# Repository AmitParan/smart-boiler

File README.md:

# Smart Electric Boiler — דוד חשמלי חכם

**An autonomous retrofit energy-management system for domestic electric water heaters.**

Final engineering project · Afeka College of Engineering, Tel Aviv
Students: **Elad Moalem** (אלעד מועלם) · **Amit Paran** (עמית פארן)
Supervisor: **Dmitry Teif** (דמיטרי טייף)

**Communication:** Master ↔ slave over **Power Line Communication** (KQ-330
modems on the 220 VAC wiring) — the default build. A WiFi (UDP) transport is
available as an option.

> ### 👨‍🏫 Reviewing this project? Start with the **[Guided Code Tour →](CODE_TOUR.md)**
> A short walkthrough of the safety architecture, the FreeRTOS mutex design, the
> wire protocol and the transport abstraction — each claim shown alongside the
> few lines of code that prove it, plus **four checks you can reproduce yourself**
> on the hardware in under ten minutes.

---

## Table of contents

1. [The problem](#1-the-problem)
2. [The solution — two-tier hybrid heating](#2-the-solution--two-tier-hybrid-heating)
3. [System architecture](#3-system-architecture)
4. [Hardware](#4-hardware)
5. [Safety architecture](#5-safety-architecture)
6. [Communication](#6-communication)
7. [Firmware architecture (FreeRTOS)](#7-firmware-architecture-freertos)
8. [The control brain](#8-the-control-brain)
9. [Repository layout](#9-repository-layout)
10. [Build and flash](#10-build-and-flash)
11. [Demo mode — 8 automated scenarios](#11-demo-mode--8-automated-scenarios)
12. [Results](#12-results)
13. [Documentation index](#13-documentation-index)

---

## 1. The problem

A conventional Israeli electric boiler ("דוד חשמלי") is a **blind, open-loop
machine**. The user flips a switch, waits, and gets no feedback about water
temperature or how much hot water is actually available. Three physical
inefficiencies follow from that:

| Problem | Consequence |
|---|---|
| **Open-loop operation** | The user over-heats "just in case", or under-heats and gets a cold shower |
| **Standing thermal losses** | A 80–150 L tank held at high temperature bleeds heat to the room continuously, 24 h a day |
| **Whole-tank heating** | Washing your hands heats 150 L of water to serve 2 L of demand |

The obvious fix — a **tankless instant heater** — is not available to most Israeli
homes. Those units demand **14 kW–24 kW** and three-phase service. A standard
apartment is limited to **single-phase, 16 A ≈ 3 kW**.

## 2. The solution — two-tier hybrid heating

This project fits **within the 3 kW household ceiling** by splitting the job
across two coordinated heating tiers instead of one big element.

```
   ┌──────────────────────────────────────────────────────────────┐
   │  TIER 1 — Moderate Storage                                   │
   │  Hold the main tank at only 35–40 °C, not 60–70 °C.          │
   │  A cooler tank loses far less heat to the room, so standing   │
   │  losses collapse. The tank is a warm buffer, not a kettle.    │
   └──────────────────────────────────────────────────────────────┘
                                │  water leaves the tank at ~35-40 °C
                                ▼
   ┌──────────────────────────────────────────────────────────────┐
   │  TIER 2 — Flow-Triggered Top-Up                              │
   │  A 3000 W inline heater in series with the outlet pipe adds   │
   │  a focused +3-7 °C ONLY while water is actually flowing,      │
   │  and only under hardware interlock. Energy is spent on the    │
   │  water you are using, at the moment you use it.               │
   └──────────────────────────────────────────────────────────────┘
```

The tank never has to be hot — it only has to be *warm enough* that a 3 kW
inline booster can close the remaining gap in real time. That is what keeps the
system inside a single-phase 16 A supply while still delivering a hot shower.

On top of the thermodynamics sits an **adaptive learning layer** that records
when the household actually showers and pre-heats ahead of predicted demand,
so the tank is ready without being held hot all day.

## 3. System architecture

Two microcontrollers, deliberately separated by role:

```
┌───────────────────────────────┐              ┌───────────────────────────────┐
│  MASTER — indoor command unit │              │  SLAVE — boiler-side unit     │
│  ESP32-S3                     │              │  ESP32-C6                     │
│  Viewe UEDX80480050E-WB-A     │◄────────────►│  custom PCB                   │
│  800x480 capacitive touch     │   1 packet   │                               │
│                               │   per second │                               │
│  · LVGL v8 touchscreen HMI    │              │  · 3x DS18B20 temperature     │
│  · SystemManager state machine│              │  · YF-B6 flow sensor          │
│  · Smart preheat learning     │              │  · ACS758 current sensing     │
│  · WiFi / NTP / weather       │              │  · 2x SSR drive (burst PWM)   │
│  · 8-scenario demo bench      │              │  · analog hardware interlock  │
└───────────────────────────────┘              └───────────────────────────────┘
        the user's world                              the plumbing's world
```

**Why two units?** The boiler is usually in a service balcony or on the roof —
behind reinforced concrete, often inside or near a MAMAD (safe room). Putting
the touchscreen there would be useless, and relying on WiFi reaching there was
judged unsafe for a control link. The control link therefore runs over **the
building's own 220 VAC wiring** using **Power Line Communication (PLC)**, which
passes through concrete that WiFi cannot.

> **Transport options.** PLC over KQ-330 modems is the default link. The
> communication layer is abstracted, so the same firmware can alternatively run
> the link over **WiFi (UDP)** with a single build flag, carrying byte-identical
> packets. Everything above the transport is shared by both options
> (see [section 6](#6-communication)).

## 4. Hardware

### 4.1 Slave GPIO map — ESP32-C6 *(book Table 7)*

| GPIO | Function | Direction | Component |
|:---:|---|---|---|
| **4** | `SSR_Internal` | Output (PWM) | Tank heater SSR |
| **5** | `SSR_Boost` | Output (PWM) | Inline booster SSR |
| **7** | `One_Wire_Bus` | In/Out | 3 × DS18B20 on one bus |
| **6** | `Flow_Sensor` | Input (interrupt) | YF-B6 Hall-effect flow meter |
| **10** | `PLC_RX` | Input (UART) | KQ-330 DOUT, via level shifter U3 |
| **11** | `PLC_TX` | Output (UART) | KQ-330 DIN |
| **3** | `Current_ADC` | Input (analog) | ACS758LCB-050B |

Defined in [`slave/src/config/config.h`](slave/src/config/config.h).

### 4.2 Master GPIO map — ESP32-S3 *(book Table 9)*

| GPIO | Function | Direction | Component |
|:---:|---|---|---|
| **17** | `MASTER_TX_PIN` | Output | KQ-330 DIN |
| **13** | `MASTER_RX_PIN` | Input | KQ-330 DOUT |
| **43 / 44** | `UART0_TX/RX` | — | USB CDC debug console |
| — | Touch + RGB | — | Managed by the board package (800×480) |

Defined in [`master/src/config/config.h`](master/src/config/config.h).

### 4.3 Key components

| Component | Part | Role |
|---|---|---|
| Master MCU | ESP32-S3 (Viewe UEDX80480050E-WB-A) | HMI, decisions, connectivity |
| Slave MCU | ESP32-C6-DevKitC-1 | Sensing, switching, safety |
| Power-line modem | KQ-330 | 9600 bps UART over 220 VAC |
| Solid-state relays | SSR-40DA (zero-crossing) | Switch both heating elements |
| Temperature | 3 × DS18B20 (1-Wire) | Tank, boiler outlet, boost outlet |
| Flow | YF-B6 Hall-effect | `F = 6.6 × Q` (Hz per L/min) |
| Current | ACS758LCB-050B | 40 mV/A, power calculation + fault detection |
| Comparator | LM393N + NTC | Autonomous 85 °C thermal cutoff |
| Interlock switching | 2N2222A BJT, BS170 MOSFET | Watchdog and flow gates |
| Level shifter | SN74LV1T34 | 5 V ↔ 3.3 V on the modem link |
| PSU | HLK-10M05 | 220 VAC → 5 V, isolated |

Full schematic, Gerbers, drill files and BOM live in [`pcb/`](pcb/).
Datasheets for every part are in [`datasheets/`](datasheets/).

## 5. Safety architecture

Safety is **dual-layer**: fast software checks, plus an **analog hardware
envelope that works even if the microcontroller is dead**. This is the heart of
the project and the reason the design is defensible.

### 5.1 The four hardware gates *(book §9.1.4)*

| Gate | Built from | What it physically prevents |
|---|---|---|
| **a. Internal Watchdog Gate** | 2N2222A BJT + DC-blocking capacitor | Controller freeze. The SSR latches **only** while it receives a continuous 1 kHz pulse train. A frozen MCU leaves a constant DC level, the capacitor blocks it, the base charge bleeds away and the heater is cut within ≈1 s. |
| **b. External Boost Gate** | Watchdog + flow interlock + PWM | Triple-gated. The booster cannot energise unless the controller is alive **and** water is genuinely flowing. |
| **c. Flow Interface** | BS170 MOSFET, 15–60 Hz | Dry-fire protection. When flow pulses stop, the RC network discharges and cuts the booster within 1.0 s. |
| **d. Analog Comparator + Thermal Cutoff** | LM393N + NTC, V<sub>ref</sub> ≈ 0.63 V | Boiling. At ≈85 °C the comparator output flips and disconnects SSR power directly — **no firmware involved at all**. |

> **This is why `ledcWrite(pin, 127)` at 1 kHz is not optional.**
> It looks like a PWM power setting; it is actually the **carrier that proves the
> controller is alive** to gate (a). Replacing it with `digitalWrite(HIGH)` would
> be read by the hardware as a controller-freeze fault and the heater could never
> stay on. See [`slave/src/tasks/pwm_task_internal.cpp`](slave/src/tasks/pwm_task_internal.cpp).

### 5.2 Hardware truth table *(book Table 11)*

`1` = live PWM pulse train · `DC/0` = logic low / fault / blocked · `X` = don't care

| NTC safety | CMD internal | CMD boost | Flow | SSR internal | SSR boost | Meaning |
|:---:|:---:|:---:|:---:|:---:|:---:|---|
| 0 (overheat) | X | X | X | **0** | **0** | NTC disconnects everything — system-wide safe state |
| 1 (OK) | DC / 0 | DC / 0 | X | 0 | 0 | Idle — no commands from the controller |
| 1 (OK) | 1 | DC / 0 | X | **1** | 0 | Base tank heating, independent of flow |
| 1 (OK) | DC / 0 | 1 | 1 | 0 | **1** | Booster only — requires flow |
| 1 (OK) | X | X | **0** | X | **0** | Flow interlock forces the booster off |
| 1 (OK) | 1 | 1 | 1 | **1** | **1** | Both tiers active under hardware supervision |

### 5.3 Software safety — `TaskSafety`, every 50 ms

[`slave/src/tasks/safety_task.cpp`](slave/src/tasks/safety_task.cpp) runs at the
**highest FreeRTOS priority (4)** and independently verifies:

1. Every temperature sensor is below **80 °C** (software cutoff, below the 85 °C hardware trip)
2. The booster is never commanded while flow **< 1.0 L/min** (dry-fire)
3. No **uncommanded current** is flowing — catches a welded/shorted SSR
4. A **CMD packet arrived within the last 5 s** — otherwise the link is presumed lost
5. Every temperature reading is **physically plausible** (−55…+125 °C) — a
   disconnected DS18B20 reports −127 °C, which would otherwise convince the
   controller the water is freezing and make it heat indefinitely while check 1
   stays silent. A failed sensor must stop the heater, not command full power.

Any failure latches `system_fault`, and both SSRs are cut immediately.

## 6. Communication

### 6.1 Binary packet protocol

Frame layout, identical on both sides
([`*/src/config/boiler_protocol.h`](slave/src/config/boiler_protocol.h)):

```
[ 0xAA | LEN | TYPE | SEQ | ...payload... | CRC8 | 0x55 ]
  start                                            end
         └────── CRC-8/SMBUS (poly 0x07) ──────┘
```

| Packet | Direction | Size | Contents |
|---|---|:---:|---|
| **CMD** | Master → Slave | 9 B | PWM internal %, PWM boost %, flag bits |
| **STATUS** | Slave → Master | 17 B | 3 × temperature, flow, power, status bits |

Temperatures are sent as `int16 × 10` (0.1 °C resolution), flow as `uint16 × 10`.
Cadence is **1 packet per second**, with a rolling sequence number so either side
detects a dropped packet.

### 6.2 The transport layer — PLC, with a WiFi option

The master and slave communicate over **Power Line Communication**: each board
drives a KQ-330 modem over UART (9600 bps), and the modems carry the packets
across the 220 VAC mains wiring. The link medium is abstracted behind
[`link.h`](slave/src/comms/link.h), so the **exact same bytes** can alternatively
travel over WiFi.

The PLC link was verified working on the bench: a CMD every second, a STATUS
reply, CRC-8 validation and sequence numbers, with the KQ-330 timing constants
(2 ms/byte, 200 ms half-duplex guard) locked in firmware.

```
       sendCommand() / PLC_SendStatus()          ← protocol, unchanged
                     │
          link_send() / link_poll()              ← the abstraction
                     │
           ┌─────────┴─────────┐
     link_plc.cpp        link_wifi.cpp
   KQ-330 over UART        UDP over WiFi
```

| | `link_plc.cpp` **(default)** | `link_wifi.cpp` (option) |
|---|---|---|
| Framing | Byte-by-byte receive state machine | A datagram **is** a frame |
| TX timing | 2 ms inter-byte gap (modem requirement) | none |
| Half-duplex guard | 200 ms after RX before TX | none — UDP is full duplex |
| Discovery | n/a | Automatic; no IP is configured anywhere |

Selected by one build flag in `platformio.ini` — **the same on both sides**:

```ini
build_flags =
    ; -DLINK_WIFI    ; flag absent (default) -> KQ-330 power-line modem
                     ; uncomment             -> WiFi (UDP)
```

### 6.3 PLC installation notes

- Both KQ-330 modems must be on the **same electrical phase** of the mains.
- The modem is half-duplex, so the protocol is strictly master-initiated
  request/response, with a 200 ms guard before the slave replies.
- Bytes are paced 2 ms apart, as the modem requires.

A step-by-step procedure for checking the modem link during installation is in
[`TROUBLESHOOTING_PLC.md`](TROUBLESHOOTING_PLC.md).

## 7. Firmware architecture (FreeRTOS)

### 7.1 Slave task hierarchy *(book Table 19)*

| Priority | Task | Period | Responsibility |
|:---:|---|---|---|
| **4** (highest) | `TaskSafety` | 50 ms | Closed-loop safety, hard SSR cutoff |
| **3** | `TaskPWM_Internal`, `TaskPWM_Boost` | 2000 ms window | Burst-mode SSR power control |
| **2** | `TaskTemp`, `TaskFlow`, `TaskCurrent`, `TaskPLC` | 100–500 ms | Sensing and the comms link |
| **1** (lowest) | `TaskSerial` | loop | Debug console, `d`/`r` mode switching |

### 7.2 Memory guards — the four mutexes *(book Table 20)*

The slave is fully concurrent, so every shared variable is protected:

| Mutex | Written by | Read by |
|---|---|---|
| `guard_temps` | `TaskTemp` | `TaskPLC`, `TaskSafety`, `TaskPWM_Boost` |
| `guard_flow` | `TaskFlow` | `TaskPLC`, `TaskSafety`, `TaskPWM_Boost` |
| `guard_current` | `TaskCurrent` | `TaskPLC`, `TaskSafety` |
| `guard_cmd` | `TaskPLC` | `TaskPWM_Internal`, `TaskPWM_Boost`, `TaskSafety` |

Created in [`slave/src/main.cpp`](slave/src/main.cpp) **before any task starts**.

### 7.3 Master — dual-core split *(book Table 17)*

The ESP32-S3's two cores are separated deliberately so that a heavy LVGL redraw
can never delay a control packet:

| Core | Work |
|---|---|
| **Core 0** | `TaskMasterComms` — 1 s CMD cadence, STATUS reception, CRC-8 |
| **Core 1** | LVGL GUI, touch, WiFi/NTP, weather, automated test bench |

### 7.4 Burst-mode power control

The booster must deliver a *specific* power, not simply on/off. Required power
comes from the thermodynamic relation:

```
P = ṁ · Cp · ΔT
```

For 5 L/min (ṁ = 0.0833 kg/s) and ΔT = 6 °C:
`P = 0.0833 × 4184 × 6 ≈ 2090 W` — about **70 %** of the 3000 W element.

The controller therefore runs a **2000 ms time-proportional window**: 1400 ms ON,
600 ms OFF. Because the SSR is zero-crossing, a 2 s window contains 200 mains
half-cycles at 50 Hz, so 70 % resolves to 140 half-cycles — fine-grained control
with no switching noise injected onto the power line.

```
Power envelope   ████████████████████░░░░░░░░    1400 ms ON / 600 ms OFF
1 kHz carrier    ▌▌▌▌▌▌▌▌▌▌▌▌▌▌▌▌▌▌▌▌            watchdog proof-of-life
Mains output     ∿∿∿∿∿∿∿∿∿∿∿∿∿∿∿∿∿∿∿∿            switched at zero crossings
```

## 8. The control brain

### 8.1 SystemManager — finite state machine

[`master/src/control/SystemManager.cpp`](master/src/control/SystemManager.cpp)
evaluates in strict priority order:

| Priority | State | Trigger | Output |
|:---:|---|---|---|
| 1 | `SAFETY_OVERRIDE` | Link lost **or** T ≥ 85 °C | Both PWM = 0 |
| 2 | `STATE_OFF` | User switched off | Both PWM = 0 |
| 3 | `STATE_SHOWER_BOOST` | Flow detected **and** tank < 45 °C | Booster on |
| 4 | `STATE_HEATING_TANK` | No flow **and** tank < 40 °C | Tank heater on |
| 5 | `STATE_STANDBY` | Temperature satisfied | Idle |

### 8.2 Smart preheat — the learning layer

[`master/src/control/smart_preheat.cpp`](master/src/control/smart_preheat.cpp)
records the time of each real shower (detected as flow crossing the threshold
from zero) and predicts when the household will next want hot water, starting
the tank early enough to be ready. It **never** overrides a manual ON, **never**
touches safety, and stands down entirely if the link to the slave is lost.

Three user-selectable operating modes:

| Mode | Behaviour |
|---|---|
| **Manual** | Reactive only, no pre-heating |
| **Ready-by** | User sets target times; the system computes when to start |
| **Smart** | Learned usage patterns drive pre-heating automatically |

## 9. Repository layout

Both firmwares use the same scheme, so understanding one gets you the other.

```
master/src/                              slave/src/
├── main.cpp      boot, WiFi/NTP,        ├── main.cpp      boot, mutexes,
│                 LVGL render loop       │                 task creation
├── config/       pins, wire protocol,   ├── config/       pins, wire protocol,
│                 LVGL + display config  │                 ports, WiFi secrets
├── comms/        transport + task       ├── comms/        transport + protocol
├── control/      SystemManager, smart   ├── core/         shared state, mutexes,
│                 preheat, app mode      │                 DEMO/REALTIME mode
├── data/         statistics, network    ├── tasks/        6 FreeRTOS tasks
├── ui/           LVGL screens           └── diagnostics/  test sketches
├── demo/         8-scenario bench
└── diagnostics/  test sketches
```

### Where do I look for…?

| Question | File |
|---|---|
| What decides when the heater turns on? | `master/src/control/SystemManager.cpp` |
| What do master and slave send each other? | `*/src/config/boiler_protocol.h` |
| How do the bytes travel? | `*/src/comms/link.h`, `link_plc.cpp`, `link_wifi.cpp` |
| How is an SSR actually switched? | `slave/src/tasks/pwm_task_internal.cpp` |
| What protects against overheating? | `slave/src/tasks/safety_task.cpp` |
| Where are the demo scenarios? | `master/src/demo/demo_scenarios.cpp` |
| Which GPIO is what? | `*/src/config/config.h` |
| How does the learning work? | `master/src/control/smart_preheat.cpp` |

> **Note on `#include`:** every include stays short (`#include "config.h"`)
> because each `platformio.ini` adds the `src/` subfolders to the include path.
> No source file needed editing when the folders were introduced.

## 10. Build and flash

Requires [PlatformIO](https://platformio.org/). Both projects are independent.

```bash
# Slave (ESP32-C6)
cd slave
pio run --target upload
pio device monitor
```

```bash
# Master (ESP32-S3)
cd master
pio run --target upload
pio device monitor
```

Set `upload_port` / `monitor_port` in each `platformio.ini` to your actual COM
ports (`pio device list` will show them).

### WiFi option — credentials (slave)

Only needed when building with `-DLINK_WIFI`. The slave has no touchscreen, so
its credentials are compiled in:

```bash
cd slave/src/config
cp wifi_secrets.example.h wifi_secrets.h    # then edit with your SSID/password
```

`wifi_secrets.h` is **gitignored** and never reaches GitHub. ESP32 radios are
**2.4 GHz only** — a 5 GHz-only network will not connect.

### Windows build note

`slave/platformio.ini` sets `core_dir = C:/pio`. This is **required on Windows**:
RISC-V gcc forwards all 278 framework include paths to the assembler, and with
`<WiFi.h>` included (WiFi option) the command line reaches 32,870 characters against Windows'
32,767 limit — reported misleadingly as `cannot execute as.exe`. Create the short
path once (no admin needed):

```bash
mklink /J C:\pio %USERPROFILE%\.platformio
```

## 11. Demo mode — 8 automated scenarios

The master runs a complete automated test bench
([`master/src/demo/demo_scenarios.cpp`](master/src/demo/demo_scenarios.cpp)) that
injects scripted sensor values, so the **entire control and safety chain can be
demonstrated without plumbing or 220 V loads**. The slave still fires its real
SSRs, so the behaviour is genuine end-to-end.

| # | Scenario | Demonstrates |
|:---:|---|---|
| 1 | Pre-Heating (tank only) | `STATE_HEATING_TANK`, internal SSR, 2500 W |
| 2 | Preheated Shower | `STATE_SHOWER_BOOST`, booster SSR, 3000 W |
| 3 | Warm Shower Boost Cutoff | Both SSRs off once 45 °C is reached |
| 4 | Standby / Redundant Request | Correct idle, 0 W |
| 5 | Predictive Solar Bypass | System yields to solar gain, stays off through a 28→42 °C sweep |
| 6 | Communication Loss | Link cut → slave 5 s watchdog → hard cutoff |
| 7 | Overtemperature | Software cutoff at 80 °C, hardware interlock simulated at 85 °C |
| 8 | Stuck SSR | Uncommanded current detected within 50 ms |

Switch modes from the Settings screen, or on the slave console: `d` = DEMO,
`r` = REALTIME, `?` = status.

## 12. Results

- **30–50 % reduction** in daily electricity consumption versus a conventional
  boiler, while fully preserving user comfort
- Validated on a laboratory test bench **and** through MATLAB/Simulink
  system-level simulation across all operating scenarios and edge cases
- Communication robustness and immediate safety response demonstrated
- Operates entirely within a standard **single-phase 16 A / 3 kW** household supply

The complete energy analysis, simulation models and scenario plots are in
[`Matlab/`](Matlab/).

## 13. Documentation index

| Path | Contents |
|---|---|
| [`README_v3.md`](README_v3.md) | Detailed development documentation, bug log, TODO |
| [`SYSTEM_DOCUMENTATION.md`](SYSTEM_DOCUMENTATION.md) | System-level reference |
| [`docs/plc-protocol.md`](docs/plc-protocol.md) | Packet protocol specification |
| [`docs/smart-brain.md`](docs/smart-brain.md) | Learning algorithm design |
| [`docs/smart-preheat.md`](docs/smart-preheat.md) | Pre-heat decision logic |
| [`TROUBLESHOOTING_PLC.md`](TROUBLESHOOTING_PLC.md) | KQ-330 link installation and check procedure |
| [`pcb/`](pcb/) | Schematic, board layout, Gerbers, drill files, BOM |
| [`datasheets/`](datasheets/) | Datasheets for every component used |
| [`Matlab/`](Matlab/) | Simulink model, 8 scenario scripts, energy analysis |
| [`tools/`](tools/) | `serial_logger.py`, `udp_link_probe.py` (WiFi option) |

---

<sub>Afeka College of Engineering, Tel Aviv · Final Engineering Project</sub>

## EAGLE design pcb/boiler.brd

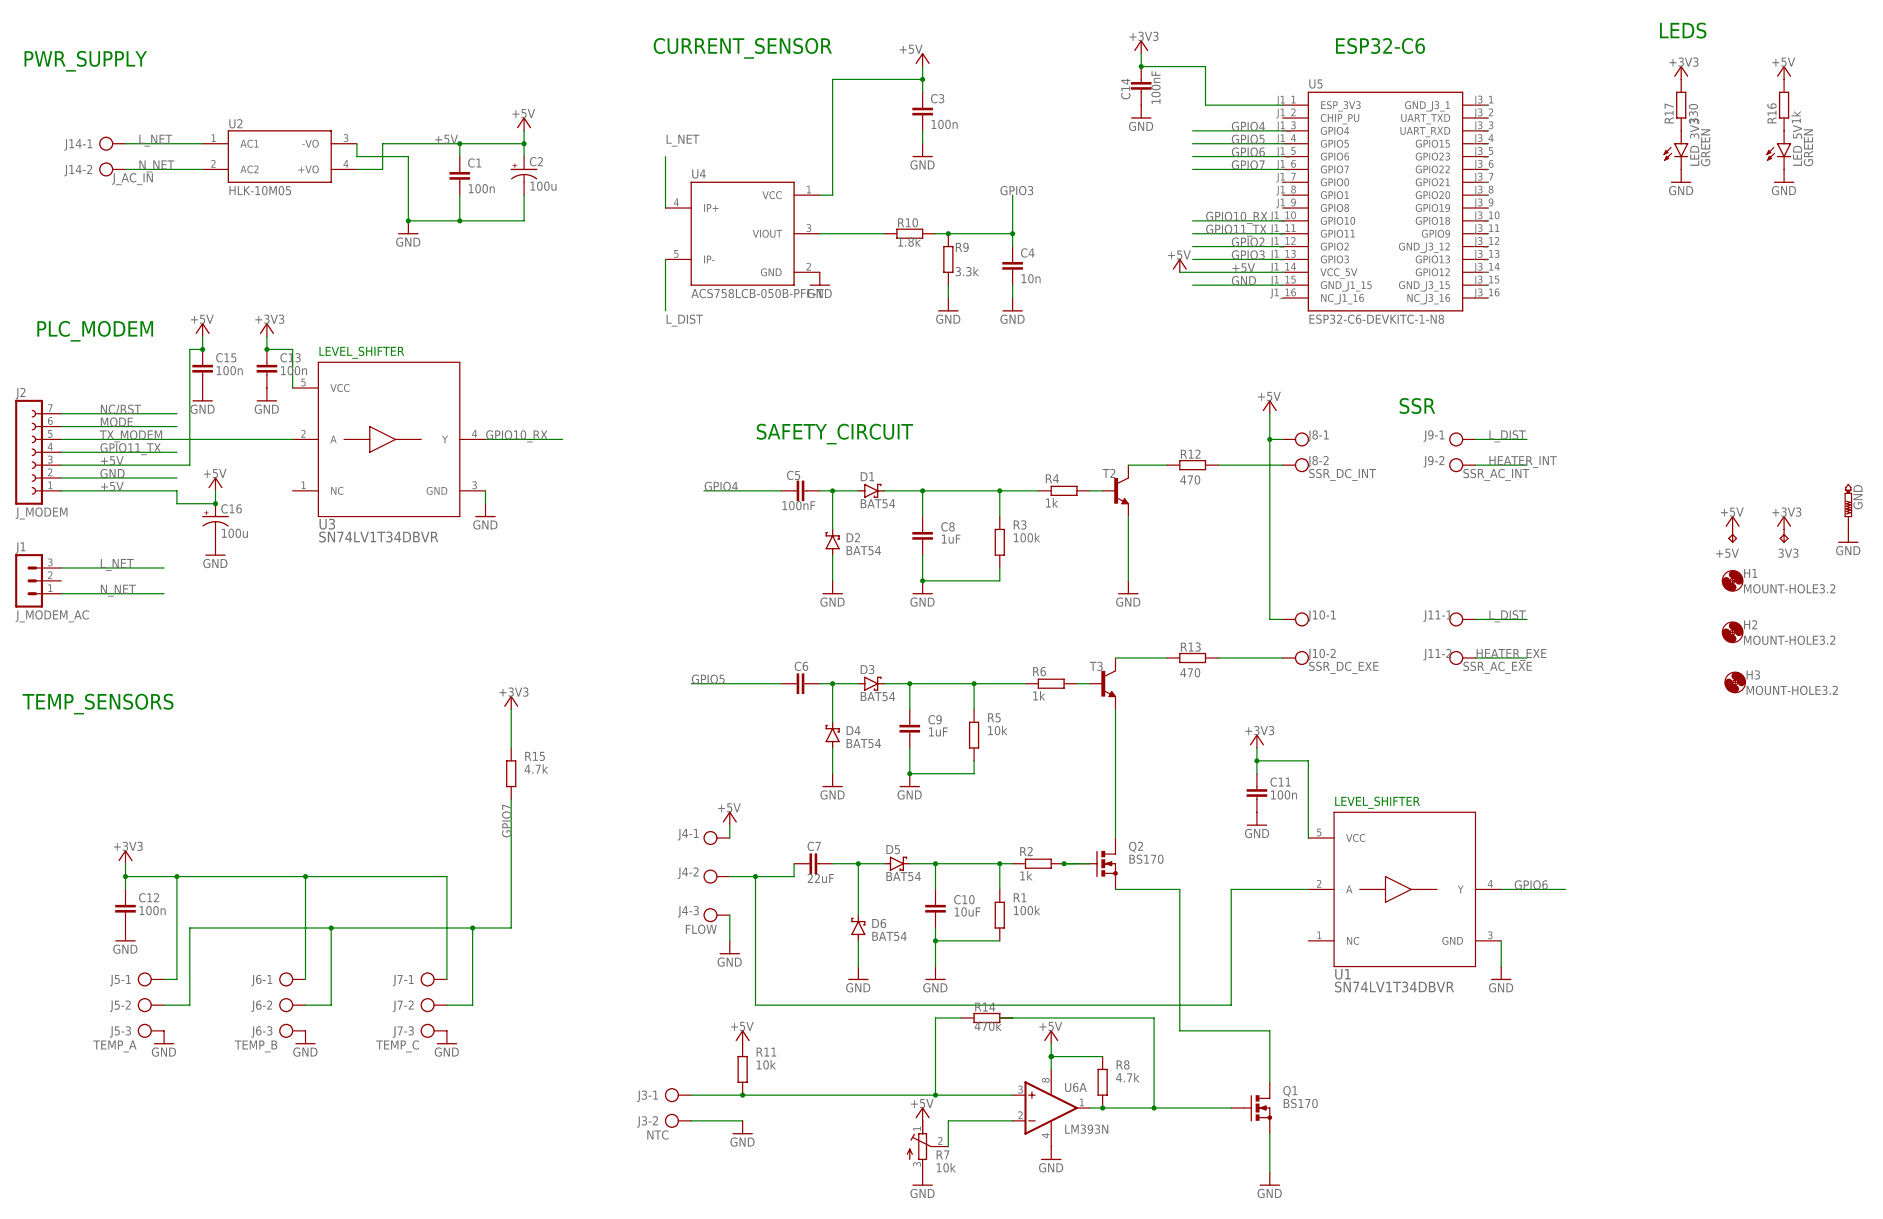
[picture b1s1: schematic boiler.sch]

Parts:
3V3: TPB2,54; B2,54
+5V: TPB2,54; B2,54
C1, C3, C11, C12, C13, C15: 100n; C0603
C2, C16: 100u; PANASONIC_C
C4: 10n; C0603
C5, C14: 100nF; C0603
C6: 1u; C0603
C7: 22uF; C0603
C8, C9: 1uF; C0603
C10: 10uF; C0603
D1, D2, D3, D4, D5, D6: BAT54; SOT23
GND: PTR1TP15R; TP15R
H1, H2, H3: MOUNT-HOLE3.2; 3,2
J1: J_MODEM_AC; MA03-1
J2: J_MODEM; FE07
J3: NTC; AK500/2
J4: FLOW; AK500/3
J5: TEMP_A; AK500/3
J6: TEMP_B; AK500/3
J7: TEMP_C; AK500/3
J8: SSR_DC_INT; AK500/2
J9: SSR_AC_INT; AK500/2
J10: SSR_DC_EXE; AK500/2
J11: SSR_AC_EXE; AK500/2
J14: J_AC_IN; AK500/2
LED_3V3, LED_5V: GREEN; CHIPLED_0603
Q1, Q2: BS170; SOT54E
R1, R3: 100k; R0603
R2, R4, R6, R16: 1k; R0603
R5, R11: 10k; R0603
R7: 10k; RTRIM3314G
R8, R15: 4.7k; R0603
R9: 3.3k; R0603
R10: 1.8k; R0603
R12, R13: 470; R0603
R14: 470k; R0603
R17: 330; R0603
T2, T3: 2N2222-NPN-TO92-EBC; TO92-EBC
U1, U3: SN74LV1T34DBVR; DBV0005A_N
U2: HLK-10M05; CONV_HLK-10M05
U4: ACS758LCB-050B-PFF-T; XDCR_ACS758LCB-050B-PFF-T
U5: ESP32-C6-DEVKITC-1-N8; MODULE_ESP32-C6-DEVKITC-1-N8
U6: LM393N; DIL08

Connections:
+3V3: 3V3.TP, C11.2, C12.2, C13.2, C14.2, J5.1, J6.1, J7.1, R15.2, R17.2, U1.5 (VCC), U3.5 (VCC), U5.J1_1 (ESP_3V3)
+5V: +5V.TP, C1.2, C2.+, C3.1, C15.2, C16.+, J2.1, J2.3, J4.1, J8.1, J10.1, R7.1 (E), R8.2, R11.2, R16.2, U2.4 (+VO), U4.1 (VCC), U5.J1_14 (VCC_5V), U6.8 (V+)
GND: C1.1, C2.-, C3.2, C4.2, C8.2, C9.2, C10.2, C11.1, C12.1, C13.1, C14.1, C15.1, C16.-, D2.1 (A), D4.1 (A), D6.1 (A), GND.TP, J2.2, J3.2, J4.3, J5.3, J6.3, J7.3, LED_3V3.C, LED_5V.C, Q1.S, R1.1, R3.1, R5.1, R7.3 (A), R9.1, T2.E, U1.3 (GND), U2.3 (-VO), U3.3 (GND), U4.2 (GND), U5.J1_15 (GND_J1_15), U6.4 (V-)
GND_J3_1: U5.J3_1 (GND_J3_1)
GND_J3_12: U5.J3_12 (GND_J3_12)
GND_J3_15: U5.J3_15 (GND_J3_15)
GPIO2: U5.J1_12 (GPIO2)
GPIO3: C4.1, R9.2, R10.1, U5.J1_13 (GPIO3)
GPIO4: C5.1, U5.J1_3 (GPIO4)
GPIO5: C6.1, U5.J1_4 (GPIO5)
GPIO6: U1.4 (Y), U5.J1_5 (GPIO6)
GPIO7: J5.2, J6.2, J7.2, R15.1, U5.J1_6 (GPIO7)
GPIO10_RX: U3.4 (Y), U5.J1_10 (GPIO10)
GPIO11_TX: J2.4, U5.J1_11 (GPIO11)
HEATER_EXE: J11.2
HEATER_INT: J9.2
L_DIST: J9.1, J11.1, U4.5 (IP-)
L_NET: J1.3, J14.1, U2.1 (AC1), U4.4 (IP+)
MODE: J2.6
unnamed: C7.1, J4.2, U1.2 (A)
unnamed: C5.2, D1.1 (A), D2.3 (C)
unnamed: C8.1, D1.3 (C), R3.2, R4.1
unnamed: R4.2, T2.B
unnamed: R10.2, U4.3 (VIOUT)
unnamed: C7.2, D5.1 (A), D6.3 (C)
unnamed: C10.1, D5.3 (C), R1.2, R2.1
unnamed: Q2.G, R2.2
unnamed: LED_5V.A, R16.1
unnamed: C6.2, D3.1 (A), D4.3 (C)
unnamed: C9.1, D3.3 (C), R5.2, R6.1
unnamed: R6.2, T3.B
unnamed: Q2.D, T3.E
unnamed: R13.2, T3.C
unnamed: R12.2, T2.C
unnamed: R7.2 (S), U6.2 (-IN)
unnamed: Q1.D, Q2.S
unnamed: J3.1, R11.1, R14.2, U6.3 (+IN)
unnamed: J8.2, R12.1
unnamed: J10.2, R13.1
unnamed: LED_3V3.A, R17.1
unnamed: Q1.G, R8.1, R14.1, U6.1 (OUT)
NC/RST: J2.7
N_NET: J1.1, J14.2, U2.2 (AC2)
TX_MODEM: J2.5, U3.2 (A)

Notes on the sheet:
TEMP_SENSORS
PLC_MODEM
PWR_SUPPLY
SAFETY_CIRCUIT
CURRENT_SENSOR
LEVEL_SHIFTER
ESP32-C6
SSR
LEDS

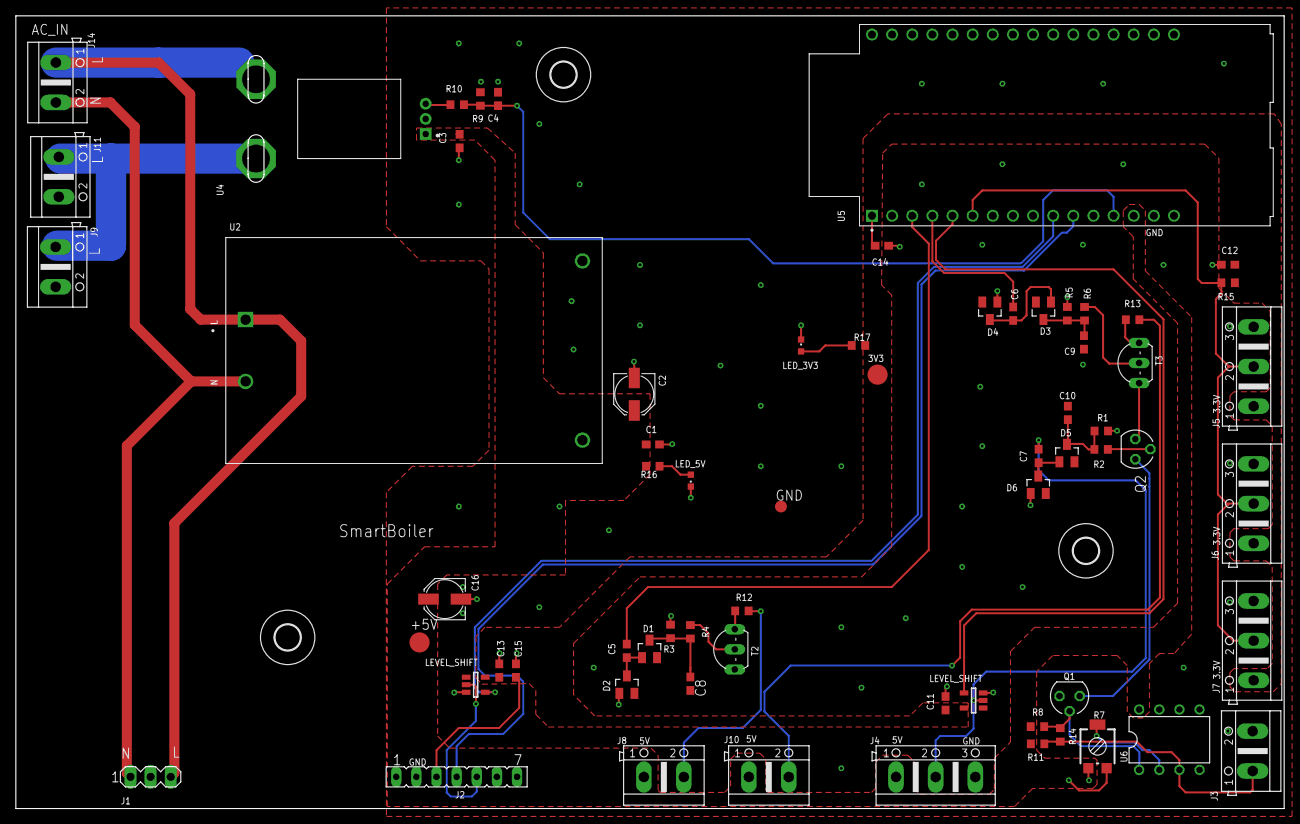
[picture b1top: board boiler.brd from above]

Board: 2 copper layers, 160.0 x 100.0 mm, 69 parts (0 on the bottom side), 36 nets.

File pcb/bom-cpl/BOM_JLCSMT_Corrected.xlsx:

Comment | Designator | Footprint | JLCPCB Part #
2N2222-NPN-TO92-EBC | T2, T3 | TO92-EBC
1.8k | R10 | R0603
100k | R1, R3 | R0603
100n | C1, C3, C11, C12, C13, C15 | C0603
100nF | C5, C14 | C0603
100u | C2, C16 | PANASONIC_C
10k | R5, R11 | R0603
10k | R7 | RTRIM3314G
10n | C4 | C0603
10uF | C10 | C0603
1k | R2, R4, R6, R16 | R0603
1u | C6 | C0603
1uF | C8, C9 | C0603
22uF | C7 | C0603
3.3k | R9 | R0603
330 | R17 | R0603
4.7k | R8, R15 | R0603
470 | R12, R13 | R0603
470k | R14 | R0603
ACS758LCB-050B-PFF-T | U4 | XDCR_ACS758LCB-050B-PFF-T
BAT54 | D1, D2, D3, D4, D5, D6 | SOT23
BS170 | Q1, Q2 | SOT54E
ESP32-C6-DEVKITC-1-N8 | U5 | MODULE_ESP32-C6-DEVKITC-1-N8
FLOW | J4 | AK500/3
GREEN | LED_3V3, LED_5V | CHIPLED_0603
HLK-10M05 | U2 | CONV_HLK-10M05
J_AC_IN | J14 | AK500/2
J_MODEM | J2 | FE07
J_MODEM_AC | J1 | MA03-1
LM393N | U6 | DIL08
MOUNT-HOLE3.2 | H1, H2, H3 | 3,2
NTC | J3 | AK500/2
PTR1TP15R | GND | TP15R
SN74LV1T34DBVR | U1, U3 | DBV0005A_N
SSR_AC_EXE | J11 | AK500/2
SSR_AC_INT | J9 | AK500/2
SSR_DC_EXE | J10 | AK500/2
SSR_DC_INT | J8 | AK500/2
TEMP_A | J5 | AK500/3
TEMP_B | J6 | AK500/3
TEMP_C | J7 | AK500/3
TPB2,54 | +5V, 3V3 | B2,54

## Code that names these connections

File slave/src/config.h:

#ifndef CONFIG_H
#define CONFIG_H

// ---------------------------------------------------------------------------
//  Temperature sensors  (DS18B20 on 1-Wire bus)
//  Index:  temps[0] = tank internal
//          temps[1] = boiler outlet
//          temps[2] = boost heater outlet
//  All three sensors share a single 1-Wire bus on GPIO7
// ---------------------------------------------------------------------------
#define PIN_TEMP_BUS          7

// ---------------------------------------------------------------------------
//  Flow sensor  (YF-B6, pulse output)
//  Signal passes through MOSFET Q2 + level shifter U1 before GPIO6
//  Must use hardware interrupt (attachInterrupt)
// ---------------------------------------------------------------------------
#define PIN_FLOW_SENSOR       6

// ---------------------------------------------------------------------------
//  Solid State Relays (AC burst-firing PWM)
//  SSR_INT passes through upper safety channel (T2 BJT)
//  SSR_EXT passes through middle safety channel (T3 BJT) + flow interlock
// ---------------------------------------------------------------------------
#define PIN_SSR_INT           4    // Internal tank heater
#define PIN_SSR_EXT           5    // External inline boost heater

// ---------------------------------------------------------------------------
//  Current sensor  (ACS758LCB-050B, 5V supply, 40mV/A, quiescent = 2.5V)
//  Raw output is divided by a 1.8kΩ / 3.3kΩ voltage divider before GPIO3
//  ADC conversion must reverse the divider — see current_task.cpp
// ---------------------------------------------------------------------------
#define PIN_CURRENT_SENSOR       3
#define CURRENT_DIVIDER_RATIO    (3.3f / 5.1f)   // R2/(R1+R2) = 3.3/(1.8+3.3)
#define ACS758_SENSITIVITY       0.040f            // 40 mV/A
#define ACS758_VREF              2.5f              // Quiescent output at 0A (VCC/2)

// ---------------------------------------------------------------------------
//  PLC modem  (KQ-330, UART — RX=GPIO10 via level shifter U3, TX=GPIO11)
// ---------------------------------------------------------------------------
#define PLC_RX_PIN            10
#define PLC_TX_PIN            11
#define PLC_BAUD              9600

// ---------------------------------------------------------------------------
//  Timing
// ---------------------------------------------------------------------------
#define STATUS_SEND_INTERVAL_MS   1000u   // slave pushes STATUS once per second

#endif // CONFIG_H

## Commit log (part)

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2025-12-02 Create 3 temp sensors
2026-03-25 Remove hardcoded weather API key
2026-03-25 Reorganize repo into master and slave projects
2026-03-25 Replace xTaskCreatePinnedToCore with xTaskCreate
2026-03-25 Optimize temperature measurement loop
    Reduced delay for sensor measurement and updated temperature reading logic.
2026-04-04 Implement current measurement task for AC RMS
2026-04-04 Add safety_task.h header file for safety task
2026-04-04 Implement safety task for system monitoring
2026-04-04 Add PWM task header file
2026-04-04 Implement PWM control task for external heater
2026-04-15 Add MATLAB/Simulink simulation: boiler model, 6 test scenarios, and documentation
2026-04-16 feat(ui): build home screen layout with all live slave packet data
    - Add bottom strip: Boost Temp (t2), Flow Rate, Showers Available, Wait Time
    - Add system mode indicator card in center column
    - Add Tank SSR / Boost SSR LED indicators in right column
    - Implement UI_UpdateSensorData() to update all widgets in one LVGL lock
    - Wire comms_master.cpp: replaced UI_UpdateWaterTemp(t1) with UI_UpdateSensorData(t1,t2,flow)
    - Add UI_UpdateBoostTemp, UI_UpdateFlowRate, UI_UpdateSystemMode, UI_UpdateSSRStatus
2026-04-16 feat(ui): consumer-first redesign - clean dashboard, shower status, demo mode
2026-04-18 feat(comms): replace JSON with binary PLC protocol (CRC-8, seq numbers)
2026-04-18 feat(comms): binary PLC protocol - fix all shared_data vars, tasks, and main
2026-04-21 fix(slave): correct ESP32-C6 pinout, board config, and current sensor ADC formula
2026-04-22 fix(slave): set upload port COM8 for ESP32-C6
2026-04-23 fix(slave): Serial2->Serial1 (ESP32-C6 has no Serial2), remove hardcoded COM port
2026-04-23 fix(slave): use OneWire git HEAD for ESP32-C6 GPIO compatibility
2026-04-23 fix(slave): pin all tasks to Core 0 - ESP32-C6 is single-core
2026-04-23 fix(slave): calibrate ACS758 zero-current at startup, fix ADC attenuation, fix Serial1 log
2026-04-24 fix(slave): init ADC pin before setting attenuation to suppress warning
2026-04-24 diag(slave): increase RX timeout to 2000ms, dump partial bytes on timeout
2026-04-26 Add pwm_task_boost.cpp file
2026-04-26 Add pwm_task_boost.h header file
2026-04-26 Add PWM task internal header file
2026-04-26 Implement PWM control task for heater management
2026-04-26 Refine comments in safety_task.cpp for safety checks
    Updated comments for clarity and accuracy regarding safety checks.
2026-04-27 fix(slave): don't TX STATUS while mid-reception (half-duplex collision fix)
2026-04-27 fix(master): change RX pin from GPIO18 to GPIO13 (SD-MISO, free pin)
2026-04-27 fix(slave): update main.cpp for split PWM tasks (internal + boost)
2026-04-27 fix(slave): add 500ms post-reception quiet time before TX to prevent end-byte collision
2026-04-27 fix(slave): request-response protocol - only TX STATUS after receiving CMD
2026-04-27 diag(slave): add raw byte counter to PLC task
2026-04-27 fix(master): remove loopback test code
2026-04-27 test(master): add SystemManager test bench (TEST_MODE flag)
2026-04-27 feat(master): dual-target energy-saving SystemManager + updated test bench
2026-04-27 test(slave): add PLC test sender task (SLAVE_TEST_MODE flag)
2026-04-27 fix(master): wire SystemManager into sendCommand() — replace stale inline PWM logic
2026-04-27 test(master): annotate master-only scenarios #1 and #4 in test bench
2026-04-27 test(slave): align 9 scenarios to match master TEST_MODE numbering/naming
2026-04-27 feat(master): unified [MASTER] log line per cycle, TEST_MODE=0 for end-to-end test
2026-04-28 chore: add [TEST FILE] banners, fix temp/current tasks, update UI info bar
2026-05-02 Complete FreeRTOS architecture refactor for Master and Slave with safety features
2026-05-02 hardware: add Eagle PCB files, schematics, gerbers, BOM and CPL for JLCPCB
2026-05-09 rename: hardware → pcb
2026-05-09 docs: update system documentation - sensor status, FreeRTOS refactor, hardware files
2026-05-09 docs: update status, add roadmap - hardware safety untested, PLC docs todo, smart decision tree planned
2026-05-09 docs: add PLC protocol documentation and datasheets folder
2026-05-09 docs: add smart brain decision tree design document
2026-05-09 docs: add weather-adjusted lead time (V3) and user-defined target time (V4) to brain design
2026-05-09 feat(brain): Phase 1 event logger - circular SPIFFS log, FLOW_START/STOP/TANK_READY hooks in comms
2026-05-09 feat(ui): shower card turns green with checkmark when water is ready
2026-05-09 feat(brain): Phase 2 shower histogram - 96-slot SPIFFS usage pattern, recorded on FLOW_START
2026-05-09 feat(brain): Phase 3 SmartBrain task - decision tree, auto preheat 30 min before predicted shower
2026-05-09 feat(brain): Phase 4 adaptive lead time - HeatupTracker rolling avg of 5 real heat-up sessions
2026-05-09 feat(brain): Phase 5 weather-adjusted lead time - inlet temp estimate, +/-2 min per deg C
2026-05-09 feat(brain): Phase 6 Ready-By time picker - user sets target time, brain back-calculates start, persisted to SPIFFS
2026-05-09 docs: complete smart brain system documentation - all 6 phases, architecture, safety, SPIFFS, testing
2026-05-11 refactor(master): reorganize src/ into logical subfolders
    - ui/ : ui_manager, lvgl_v8_port
    - system/ : SystemManager, SystemManagerTest
    - storage/ : DataManager
    - network/ : NetworkManager.h
    - tasks/ : + comms_master.cpp (was at src root)
    - task_config.h moved to src/ root (used project-wide)
2026-05-11 refactor(slave): reorganize src/ into logical subfolders
    - tasks/ : all FreeRTOS task files (flow, temp, current, safety, pwm, plc)
    - state/ : slave_state, slave_snapshots, shared_data (was shared/ + root)
    - task_config.h, main.cpp, config.h, boiler_protocol.h stay at src/ root
    - platformio.ini: add -I src so subfolder includes resolve correctly
    - All include paths updated to reflect new structure
2026-05-11 refactor(master): rename files for clarity — decision tree vs control
    Task renames:
    TaskBrain → TaskController (real-time SSR control loop)
    TaskSmartBrain → TaskPreheatScheduler (predictive 60s decision engine)
    comms_master.cpp → TaskComms.cpp (PLC communication task)
    TaskMasterComms.h → TaskComms.h
    Folder / module renames:
2026-05-31 feat(test): two-part hardware+software test platform
    Part 1 - InteractiveTestBench (master, TEST_MODE 2):
    - Serial control panel: t/f/s/on/off/plc/auto/status/reset/help commands
    - 16 auto scenarios covering all states + edge cases (flow boundary 0.5/0.51,
    temp boundary 84.9/85C, OFF beats BOOST/HEATING, SAFETY beats all)
    - Publishes to real FreeRTOS CommandSnapshot queue for live slave testing
    - Integrated into main.cpp: TEST_MODE 0=prod, 1=auto test, 2=interactive
2026-05-31 fix(slave): skip PWM tasks in HW_TEST_MODE to avoid ledcAttach conflict
2026-05-31 fix(slave): correct SlaveState_PublishCommand -> SlaveState_UpdateCommand
2026-05-31 feat(master): expand live serial output - all sensor fields + decision summary every 5s
2026-05-31 fix: master RX byte counter diagnostic + DS18B20 power-on 85C and disconnect -127C filter
2026-05-31 fix: increase command watchdog to 6000ms for half-duplex PLC
2026-06-01 fix(slave): migrate LEDC API from channel-based to pin-based (ledcAttach)
2026-06-01 refactor: unified log format [M<->S] / [S<->M] with DROP detection on both sides
2026-06-01 fix(slave): drive SSR at full DC (255) not 50% PWM — partial conduction with 127
2026-06-01 fix(slave): clamp calibrated VREF to nominal if current detected at boot
2026-06-01 fix(slave): replace LEDC with plain digitalWrite for SSR control
2026-06-01 revert(slave): restore PWM/safety/current tasks to last working state (e7b299a)
2026-06-13 docs: add comprehensive README_v3 with status, bugs, and roadmap
2026-06-13 feat(master): manual test input mode via serial console
2026-06-13 fix(master): move s_manager to file scope so handleManualInputs can access it
2026-06-13 feat(master): add combined 'set' command to change all inputs at once
2026-06-13 refactor(master): replace serial test system with 4 hardcoded test variables
2026-06-13 feat(slave): SLAVE_TEST_MODE in config.h bypasses flow interlock when testing without sensors
2026-06-13 fix(slave): SLAVE_TEST_MODE only bypasses safety interlocks, always use real PLC task
2026-06-13 fix(slave): in TEST_MODE bypass flow check in boost PWM and uncommanded-current safety check
2026-06-13 chore(slave): remove leftover SLAVE_TEST_MODE comment from main.cpp
2026-06-13 feat(system): boost cutoff at 45C; update README with test mode reference and verified status
2026-06-18 feat(slave): v4 FreeRTOS refactor - mutexes, SystemMode runtime switching, vTaskDelayUntil periodic push
2026-06-18 fix(slave): revert TaskPLC to triggered response to prevent half-duplex collision
2026-06-18 docs: update README for v4-freertos-refactor; mutex layout, SystemMode, comms pattern

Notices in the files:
parts and their libraries:
Elad: COPYRIGHT: Copyright (C) 2026 Ultra Librarian. All rights reserved.
